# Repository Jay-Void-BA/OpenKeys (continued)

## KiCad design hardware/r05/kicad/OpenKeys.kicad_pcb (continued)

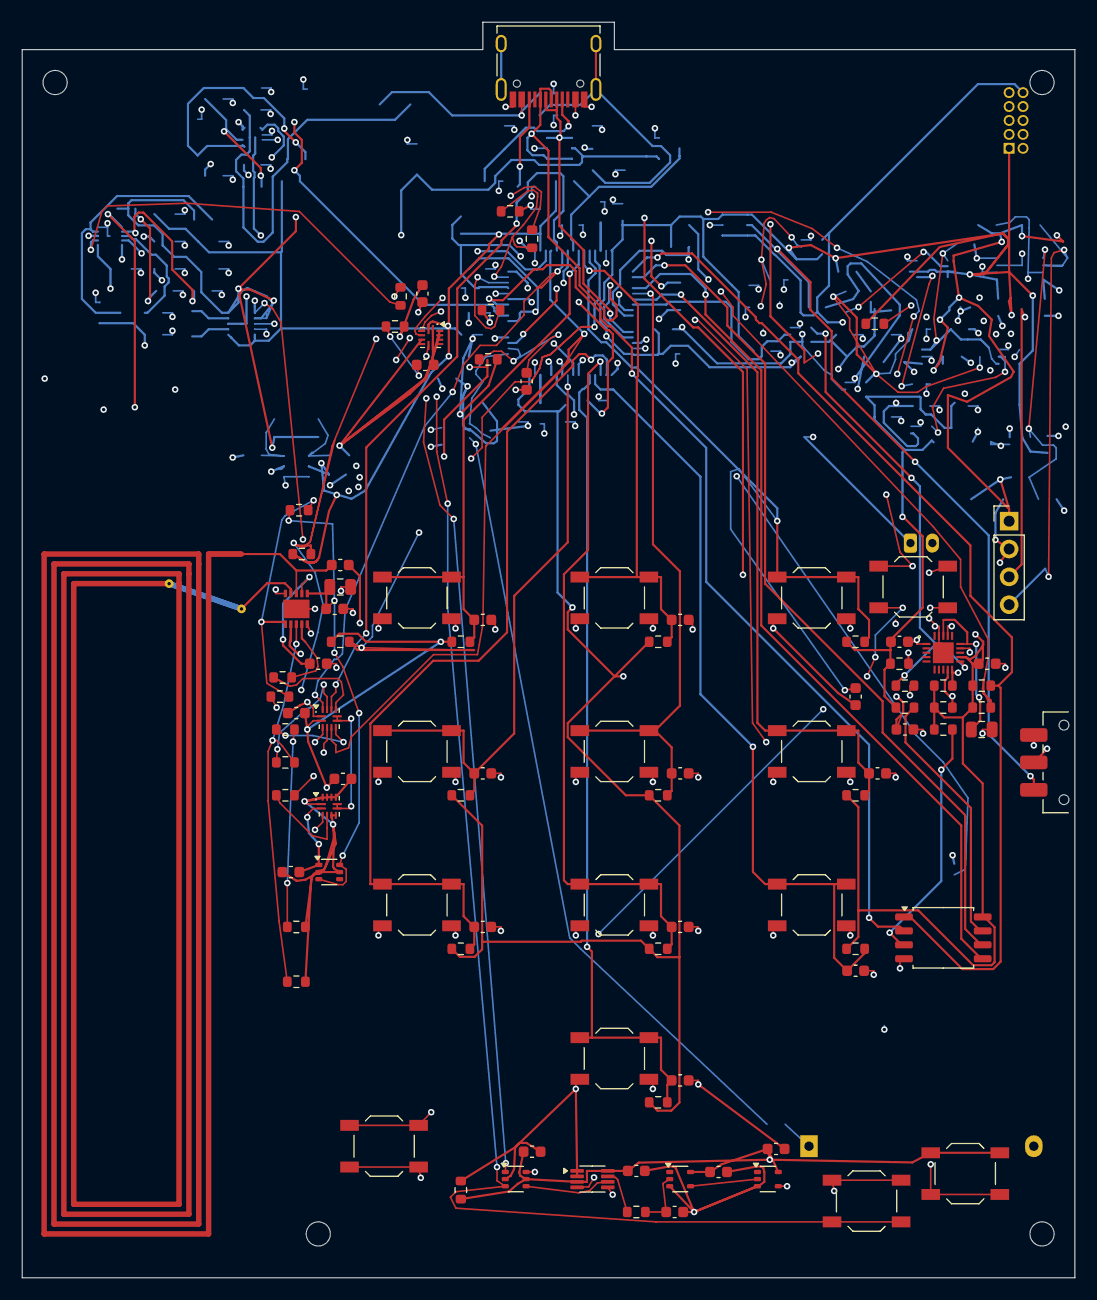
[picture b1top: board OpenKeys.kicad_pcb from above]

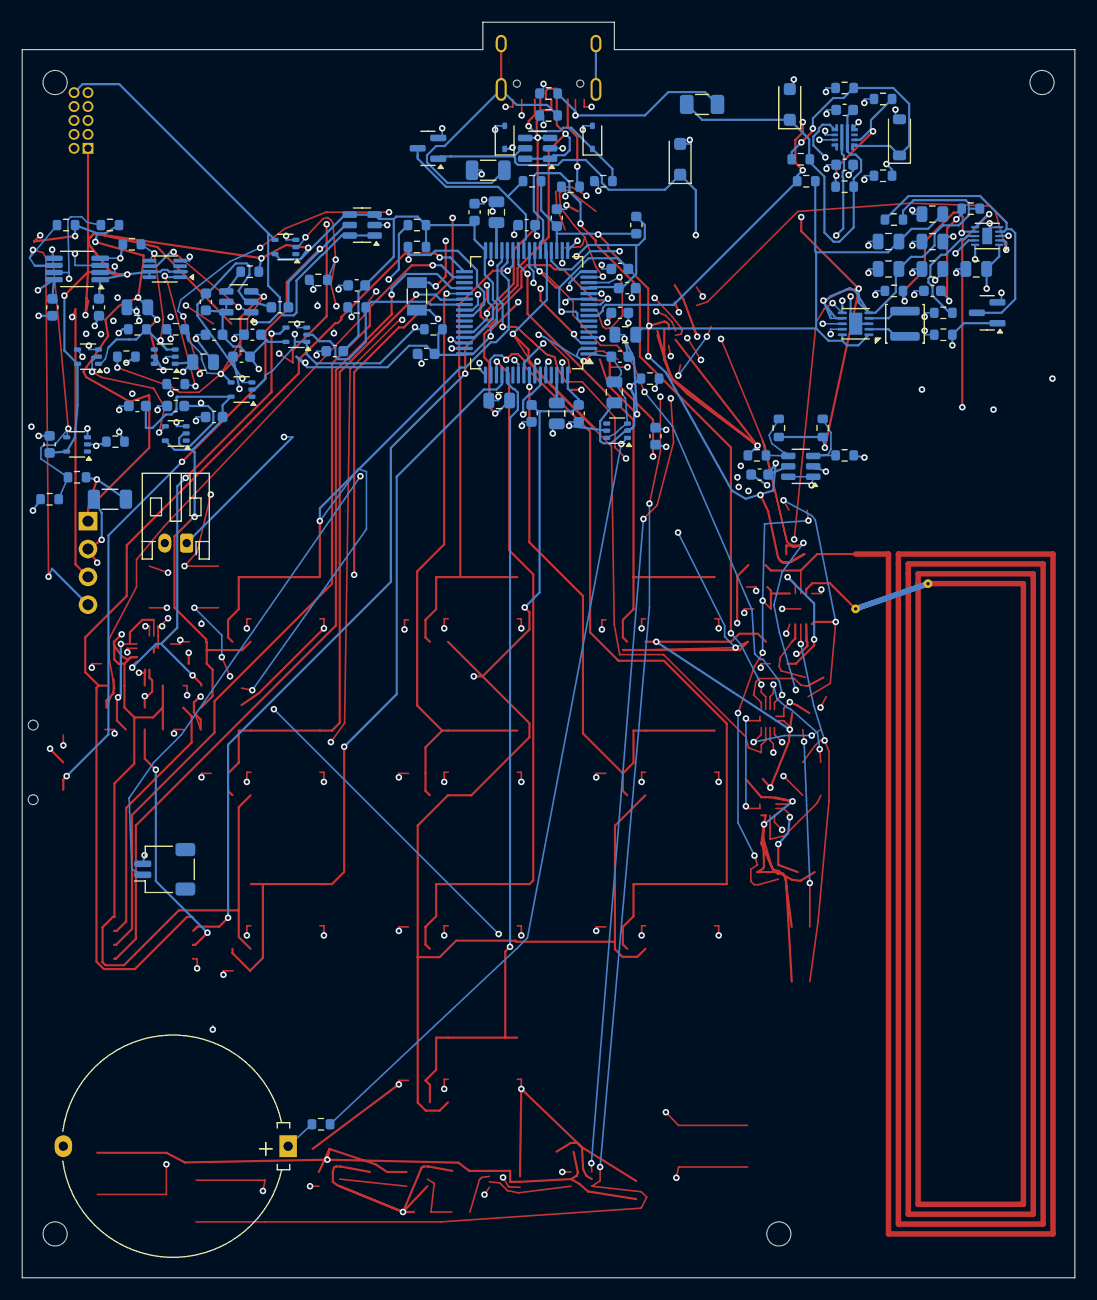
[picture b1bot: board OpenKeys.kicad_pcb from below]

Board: 4 copper layers, 96.0 x 114.5 mm, 213 parts (114 on the bottom side), 111 nets.

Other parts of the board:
H1, H2, H3, H4: MountingHole_2.2mm_M2

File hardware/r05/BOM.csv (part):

ref,value,footprint,sheet,dnp,note
J1,HRO TYPE-C-31-M-12,Connector_USB:USB_C_Receptacle_HRO_TYPE-C-31-M-12,01-usb,False,Only external data socket; qualify manufacturer drawing and sample
U1,USBLC6-2SC6,Package_TO_SOT_SMD:SOT-23-6,01-usb,False,
R1,5.1k 1%,Resistor_SMD:R_0603_1608Metric,01-usb,False,
R2,5.1k 1%,Resistor_SMD:R_0603_1608Metric,01-usb,False,
R3,1M,Resistor_SMD:R_0603_1608Metric,01-usb,False,
C1,1nF / 2kV,Capacitor_SMD:C_1206_3216Metric,01-usb,False,KEMET C1206C102KGRACTU;1206;2kV X7R10percent
Q1,2N7002,Package_TO_SOT_SMD:SOT-23,01-usb,False,
R4,100k,Resistor_SMD:R_0603_1608Metric,01-usb,False,
R5,1M,Resistor_SMD:R_0603_1608Metric,01-usb,False,
D1,SMF5.0A,Diode_SMD:D_SOD-123F,01-usb,False,
D2,PESD5V0S1BA,Diode_SMD:D_SOD-323,01-usb,False,
D3,PESD5V0S1BA,Diode_SMD:D_SOD-323,01-usb,False,
F1,250mA hold - qualify I2t,Fuse:Fuse_1206_3216Metric,02-power,False,
U2,BQ25185DLHR,Package_DFN_QFN:Texas_DLH0010A_WSON-10-1EP_2.2x2mm_P0.4mm_EP0.9x1.5mm,02-power,False,TI SLUSF65B table6-1:24k=4.2V/input100mA; ISET3k=target100mA before input DPM
J2,Adafruit 1578 protected 1S 500mAh,Connector_JST:JST_PH_S2B-PH-K_1x02_P2.00mm_Horizontal,02-power,False,Factory-protected pack; JST-PH2 polarity must be measured before mating. Pack body29x36x4.75mm; reserve32x40x6.5mm. No bare-cell substitution
J6,103AT-2 external battery thermistor,Connector_JST:JST_SH_SM02B-SRSS-TB_1x02-1MP_P1.00mm_Horizontal,02-power,False,"Semitec103AT-2 10k/B3435 insulated thermal contact to pouch, factory crimped SH harness. Not an ambient-only board thermistor"
R6,24k 1%,Resistor_SMD:R_0603_1608Metric,02-power,False,
R7,3.00k 1%,Resistor_SMD:R_0603_1608Metric,02-power,False,
R8,100k,Resistor_SMD:R_0603_1608Metric,02-power,False,
Q2,2N7002,Package_TO_SOT_SMD:SOT-23,02-power,False,
R9,100k,Resistor_SMD:R_0603_1608Metric,02-power,False,
C2,1uF 10V,Capacitor_SMD:C_0805_2012Metric,02-power,False,
C3,10uF 6.3V,Capacitor_SMD:C_0805_2012Metric,02-power,False,
C4,10uF 10V,Capacitor_SMD:C_0805_2012Metric,02-power,False,
SW1,OFF / ON,Button_Switch_SMD:SW_SPDT_CK_JS102011SAQN,02-power,False,
U3,TPS63031DSK (3.3 V),Package_SON:WSON-10-1EP_2.5x2.5mm_P0.5mm_EP1.2x2mm,02-power,False,"PS/SYNC tied to VIN: forced PWM, guaranteed DC output3.267..3.333V before load/transient effects. GND power-save mode has wider -3/+6percent range and is not approved here."
R10,0R,Resistor_SMD:R_0603_1608Metric,02-power,False,
L1,1.5uH Isat>=1.5A,Inductor_SMD:L_Sunlord_SWPA3015S,02-power,False,
C5,10uF 10V,Capacitor_SMD:C_0805_2012Metric,02-power,False,
C6,100nF,Capacitor_SMD:C_0603_1608Metric,02-power,False,
C7,10uF 6.3V,Capacitor_SMD:C_0805_2012Metric,02-power,False,
C8,10uF 6.3V,Capacitor_SMD:C_0805_2012Metric,02-power,False,
U4,STM32H573RIT6,Package_QFP:LQFP-64_10x10mm_P0.5mm,03-mcu,False,"H573 pin62=VCAP2, no PB9; SE PB6/PB7; LCD PA8/PC9. Recheck complete alternate functions before firmware target release"
C9,100nF,Capacitor_SMD:C_0603_1608Metric,03-mcu,False,
C10,100nF,Capacitor_SMD:C_0603_1608Metric,03-mcu,False,
C11,100nF,Capacitor_SMD:C_0603_1608Metric,03-mcu,False,
C12,100nF,Capacitor_SMD:C_0603_1608Metric,03-mcu,False,
C13,100nF,Capacitor_SMD:C_0603_1608Metric,03-mcu,False,
C14,4.7uF,Capacitor_SMD:C_0805_2012Metric,03-mcu,False,
C15,2.2uF low ESR,Capacitor_SMD:C_0805_2012Metric,03-mcu,False,
C16,2.2uF low ESR,Capacitor_SMD:C_0805_2012Metric,03-mcu,False,
C17,100nF,Capacitor_SMD:C_0603_1608Metric,03-mcu,False,
C18,1uF,Capacitor_SMD:C_0805_2012Metric,03-mcu,False,
FB1,600R@100MHz,Inductor_SMD:L_0603_1608Metric,03-mcu,False,
R11,10k,Resistor_SMD:R_0603_1608Metric,03-mcu,False,
C19,10nF - qualify reset timing,Capacitor_SMD:C_0603_1608Metric,03-mcu,False,
R12,10k,Resistor_SMD:R_0603_1608Metric,03-mcu,False,
J3,Internal SWD - DNP production,Connector_PinHeader_1.27mm:PinHeader_2x05_P1.27mm_Vertical,03-mcu,True,Internal manufacturing access only; close debug lifecycle before user secrets
Y1,ABS07-32.768KHZ-6-T,Crystal:Crystal_SMD_3215-2Pin_3.2x1.5mm,03-mcu,False,LSE for backup RTC and tamper. RTC validity/rollback must be qualified. 9pF loading provisional; qualify startup/drive across temperature
C20,9pF C0G - tune,Capacitor_SMD:C_0603_1608Metric,03-mcu,False,
C21,9pF C0G - tune,Capacitor_SMD:C_0603_1608Metric,03-mcu,False,
U5,SE051C2HQ1/Z01XDZ,OpenKeys:SE050_SOT1969-1_HX2QFN20,04-se-storage,False,"SE051 Rev2.0 table3/SOT1969-1: unused RF1/17 and RST14 grounded; VOUT15 to VCC18 only. Target C2 OEF A8FA/Applet7.2 full feature. Identity, PIN ACL/retries, RSA4096 and per-device SCP commissioning still require qualification"
U6,W25Q64JVSSIQ,Package_SO:SOIC-8_5.3x5.3mm_P1.27mm,04-se-storage,False,
R13,4.7k,Resistor_SMD:R_0603_1608Metric,04-se-storage,False,
R14,4.7k,Resistor_SMD:R_0603_1608Metric,04-se-storage,False,
R15,100k,Resistor_SMD:R_0603_1608Metric,04-se-storage,False,
R16,47k,Resistor_SMD:R_0603_1608Metric,04-se-storage,False,
R17,47k,Resistor_SMD:R_0603_1608Metric,04-se-storage,False,
R18,47k,Resistor_SMD:R_0603_1608Metric,04-se-storage,False,
R19,10k,Resistor_SMD:R_0603_1608Metric,04-se-storage,False,
R20,10k,Resistor_SMD:R_0603_1608Metric,04-se-storage,False,
C22,100nF,Capacitor_SMD:C_0603_1608Metric,04-se-storage,False,
C23,100nF,Capacitor_SMD:C_0603_1608Metric,04-se-storage,False,
C24,1uF,Capacitor_SMD:C_0805_2012Metric,04-se-storage,False,
C25,100nF,Capacitor_SMD:C_0603_1608Metric,04-se-storage,False,
U7,FM11NC08S (DFN10 + EP),OpenKeys:FM11NC08S_DFN10_3x3_EP1.7x2.4,05-nfc,False,"Original candidate lands from Fudan v1.0 p9: package3x3,pitch0.5,EP rotated1.7x2.4; confirm supplier revision, sample orientation, paste and DFM. All five host signals and VCC cross independent isolation on sheet13; VOUT remains local"
J4,Integral 13.56MHz PCB loop,OpenKeys:NFC_PCB_Loop_4T_62x15,05-nfc,False,Integral copper4-turn coil; no purchased connector. Separate RF-only region. Initial matching model must be measured in assembled shell.
C26,100nF,Capacitor_SMD:C_0603_1608Metric,05-nfc,False,
C27,1uF,Capacitor_SMD:C_0805_2012Metric,05-nfc,False,
C28,100nF 10V,Capacitor_SMD:C_0603_1608Metric,05-nfc,False,
C29,56pF C0G 50V initial match,Capacitor_SMD:C_0603_1608Metric,05-nfc,False,
R21,47k,Resistor_SMD:R_0603_1608Metric,05-nfc,False,
R22,47k,Resistor_SMD:R_0603_1608Metric,05-nfc,False,
J7,DFR0555 V1.1 - OFFBOARD MODULE,Connector_PinHeader_2.54mm:PinHeader_1x04_P2.54mm_Vertical,06-trusted-ui,False,Internal keyed harness must follow VCC/GND/SCL/SDA; no external second data port. Module87x32x13mm. Qualify actual supply tolerance and revision.
R23,4.7k,Resistor_SMD:R_0603_1608Metric,06-trusted-ui,False,
R24,4.7k,Resistor_SMD:R_0603_1608Metric,06-trusted-ui,False,
SW2,KEY 1,Button_Switch_SMD:SW_SPST_TL3342,06-trusted-ui,False,Independent GPIO; physical release events only. No matrix and no host key injection.
R25,47k,Resistor_SMD:R_0603_1608Metric,06-trusted-ui,False,
C30,10nF,Capacitor_SMD:C_0603_1608Metric,06-trusted-ui,False,
SW3,KEY 2,Button_Switch_SMD:SW_SPST_TL3342,06-trusted-ui,False,Independent GPIO; physical release events only. No matrix and no host key injection.
R26,47k,Resistor_SMD:R_0603_1608Metric,06-trusted-ui,False,
C31,10nF,Capacitor_SMD:C_0603_1608Metric,06-trusted-ui,False,
SW4,KEY 3,Button_Switch_SMD:SW_SPST_TL3342,06-trusted-ui,False,Independent GPIO; physical release events only. No matrix and no host key injection.
R27,47k,Resistor_SMD:R_0603_1608Metric,06-trusted-ui,False,
C32,10nF,Capacitor_SMD:C_0603_1608Metric,06-trusted-ui,False,
SW5,KEY 4,Button_Switch_SMD:SW_SPST_TL3342,06-trusted-ui,False,Independent GPIO; physical release events only. No matrix and no host key injection.
R28,47k,Resistor_SMD:R_0603_1608Metric,06-trusted-ui,False,
C33,10nF,Capacitor_SMD:C_0603_1608Metric,06-trusted-ui,False,
SW6,KEY 5,Button_Switch_SMD:SW_SPST_TL3342,06-trusted-ui,False,Independent GPIO; physical release events only. No matrix and no host key injection.
R29,47k,Resistor_SMD:R_0603_1608Metric,06-trusted-ui,False,
C34,10nF,Capacitor_SMD:C_0603_1608Metric,06-trusted-ui,False,
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
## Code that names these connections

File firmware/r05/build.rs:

use sha2::{Digest, Sha256};
use std::{env, fs, path::PathBuf};

fn main() {
    println!("cargo:rerun-if-changed=build.rs");
    let here = PathBuf::from(env!("CARGO_MANIFEST_DIR"));
    let root = here.join("../..");
    let contract = here.join("board-contract.sha256");
    println!("cargo:rerun-if-changed={}", contract.display());
    let contract = fs::read_to_string(contract).expect("R05 reviewed board contract is missing");
    assert_eq!(
        contract.lines().count(),
        2,
        "Expected PCB and pinout bindings"
    );
    let names: Vec<_> = contract
        .lines()
        .map(|row| row.split_once("  ").unwrap().1)
        .collect();
    assert_eq!(
        names,
        [
            "hardware/r05/kicad/OpenKeys.kicad_pcb",
            "hardware/r05/pinout.csv"
        ]
    );
    for row in contract.lines() {
        let (expected, name) = row.split_once("  ").expect("Invalid contract row");
        assert!(name.starts_with("hardware/r05/"));
        assert!(!name.contains(".."));
        let path = root.join(name);
        println!("cargo:rerun-if-changed={}", path.display());
        let actual = format!("{:x}", Sha256::digest(fs::read(path).unwrap()));
        assert_eq!(
            actual, expected,
            "R05 hardware changed; review and freeze a new contract"
        );
    }
    let csv = fs::read_to_string(root.join("hardware/r05/pinout.csv")).unwrap();
    let rows: Vec<Vec<&str>> = csv
        .lines()
        .skip(1)
        .map(|r| r.split(',').collect())
        .collect();
    // Independent required-function list for the diagnostic and reserved NFC
    // interface. The CSV comes from the actual MCU schematic. NFC protocol
    // operation is still disabled; checking its pins does not implement it.
    for (signal, gpio, pin, function) in [
        ("BTN1_N", "PB0", "26", "power / GPIO / dedicated"),
        ("BTN2_N", "PB1", "27", "power / GPIO / dedicated"),
        ("BTN3_N", "PB2", "28", "power / GPIO / dedicated"),
        ("BTN4_N", "PB5", "57", "power / GPIO / dedicated"),
        ("BTN5_N", "PC6", "37", "power / GPIO / dedicated"),
        ("BTN6_N", "PC7", "38", "power / GPIO / dedicated"),
        ("BTN7_N", "PA15", "50", "power / GPIO / dedicated"),
        ("BTN8_N", "PC10", "51", "power / GPIO / dedicated"),
        ("BTN9_N", "PC11", "52", "power / GPIO / dedicated"),
        ("BTN0_N", "PC12", "53", "power / GPIO / dedicated"),
        ("LCD_RELEASE", "PC3", "11", "power / GPIO / dedicated"),
        ("LCD_ARM_CLK", "PC4", "24", "power / GPIO / dedicated"),
        ("LCD_HOST_SCL", "PA8", "41", "I2C3_SCL AF4"),
        ("LCD_HOST_SDA", "PC9", "40", "I2C3_SDA AF4"),
        ("SE_ENABLE_REQUEST", "PC8", "39", "power / GPIO / dedicated"),
        ("CHARGE_ENABLE", "PB4", "56", "power / GPIO / dedicated"),
        (
            "CASE_TAMP_RETURN",
            "PC13",
            "2",
            "TAMP_IN1 dedicated/VBAT; active loop from OUT4",
        ),
        (
            "TAMP_DRIVE_RAW",
            "PA1",
            "15",
            "TAMP_OUT4 dedicated/VBAT; no GPIO waveform",
        ),
        (
            "BATTERY_SENSE",
            "PA0",
            "14",
            "ADC1_INP0 analog; main cell voltage only",
        ),
        ("USB_GUARD_FAULT_N", "PC0", "8", "power / GPIO / dedicated"),
        ("FLASH_CS_N", "PB12", "33", "power / GPIO / dedicated"),
        ("FLASH_SCK", "PB13", "34", "SPI2_SCK AF5"),
        ("FLASH_MOSI", "PB15", "36", "SPI2_MOSI AF5"),
        ("FLASH_MISO", "PC2", "10", "SPI2_MISO AF5"),
        ("NFC_CS_N", "PA4", "20", "power / GPIO / dedicated"),
        ("NFC_SCK", "PA5", "21", "SPI1_SCK AF5"),
        ("NFC_MISO", "PA6", "22", "SPI1_MISO AF5"),
        ("NFC_MOSI", "PA7", "23", "SPI1_MOSI AF5"),
        ("NFC_IRQ_N", "PB10", "29", "power / GPIO / dedicated"),
    ] {
        let matching: Vec<_> = rows.iter().filter(|r| r[2] == signal).collect();
        assert_eq!(
            matching.len(),
            1,
            "Missing or duplicate R05 signal: {signal}"
        );
        assert_eq!(matching[0][0], pin);
        assert_eq!(matching[0][1], gpio);
        assert_eq!(matching[0][3], function);
    }
    assert!(!csv.contains("FP_") && !csv.contains("LCD_RESET_N"));
    assert!(
        rows.iter().all(|row| row[1] != "PC1"),
        "PC1 is unused, not backup tamper"
    );
    if env::var_os("CARGO_FEATURE_R05_DIAGNOSTICS").is_none() {
        return;
    }
    assert_eq!(env::var("TARGET").unwrap(), "thumbv8m.main-none-eabihf");
    let output = PathBuf::from(env::var_os("OUT_DIR").unwrap());
    // Bring-up ONLY. Never use this OPEN/TZEN=0 map for owner secrets.
    fs::write(output.join("memory.x"), "MEMORY {\n FLASH : ORIGIN = 0x08000000, LENGTH = 2048K\n RAM : ORIGIN = 0x20000000, LENGTH = 256K\n}\n").unwrap();
    println!("cargo:rustc-link-search={}", output.display());
    println!("cargo:rustc-link-arg-bin=openkeys-r05-diagnostics=-Tlink.x");
}

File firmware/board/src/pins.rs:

// Generated from the frozen R04 pinout.csv; do not infer a different pinmux.
// Board SHA256: 6c2a93a63f343cf0401eae8c92dc1da6f5db145604ee9b0e8b9bd08b76f4bde4
#[derive(Clone, Copy, Debug, PartialEq, Eq)]
pub struct Pin {
    pub package_pin: u8,
    pub port: u8,
    pub bit: u8,
    pub alternate: Option<u8>,
}
pub const BOARD_REVISION: &str = "0.4";
pub const BOARD_SHA256: &str = "6c2a93a63f343cf0401eae8c92dc1da6f5db145604ee9b0e8b9bd08b76f4bde4";
pub const PINOUT_SHA256: &str = "015f236a2066e38bd63a31aea3ea134474402bfe2becfdf4af9b7557d0dacac5";
pub const CASE_CLOSED: Pin = Pin {
    package_pin: 2,
    port: b'C',
    bit: 13,
    alternate: None,
};
pub const LSE_IN: Pin = Pin {
    package_pin: 3,
    port: b'C',
    bit: 14,
    alternate: None,
};
pub const LSE_OUT: Pin = Pin {
    package_pin: 4,
    port: b'C',
    bit: 15,
    alternate: None,
};
pub const USB_GUARD_FAULT_N: Pin = Pin {
    package_pin: 8,
    port: b'C',
    bit: 0,
    alternate: None,
};
pub const NRST: Pin = Pin {
    package_pin: 9,
    port: b'C',
    bit: 1,
    alternate: None,
};
pub const FLASH_MISO: Pin = Pin {
    package_pin: 10,
    port: b'C',
    bit: 2,
    alternate: Some(5),
};
pub const LCD_RESET_N: Pin = Pin {
    package_pin: 11,
    port: b'C',
    bit: 3,
    alternate: None,
};
pub const CHG_STAT1_N: Pin = Pin {
    package_pin: 16,
    port: b'A',
    bit: 2,
    alternate: None,
};
pub const CHG_STAT2_N: Pin = Pin {
    package_pin: 17,
    port: b'A',
    bit: 3,
    alternate: None,
};
pub const NFC_CS_N: Pin = Pin {
    package_pin: 20,
    port: b'A',
    bit: 4,
    alternate: None,
};
pub const NFC_SCK: Pin = Pin {
    package_pin: 21,
    port: b'A',
    bit: 5,
    alternate: Some(5),
};
pub const NFC_MISO: Pin = Pin {
    package_pin: 22,
    port: b'A',
    bit: 6,
    alternate: Some(5),
};
pub const NFC_MOSI: Pin = Pin {
    package_pin: 23,
    port: b'A',
    bit: 7,
    alternate: Some(5),
};
pub const LCD_BACKLIGHT: Pin = Pin {
    package_pin: 24,
    port: b'C',
    bit: 4,
    alternate: None,
};
pub const VBUS_PRESENT_N: Pin = Pin {
    package_pin: 25,
    port: b'C',
    bit: 5,
    alternate: None,
};
pub const BTN1_N: Pin = Pin {
    package_pin: 26,
    port: b'B',
    bit: 0,
    alternate: None,
};
pub const BTN2_N: Pin = Pin {
    package_pin: 27,
    port: b'B',
    bit: 1,
    alternate: None,
};
pub const BTN3_N: Pin = Pin {
    package_pin: 28,
    port: b'B',
    bit: 2,
    alternate: None,
};
pub const NFC_IRQ_N: Pin = Pin {
    package_pin: 29,
    port: b'B',
    bit: 10,
    alternate: None,
};
pub const FLASH_CS_N: Pin = Pin {
    package_pin: 33,
    port: b'B',
    bit: 12,
    alternate: None,
};
pub const FLASH_SCK: Pin = Pin {
    package_pin: 34,
    port: b'B',
    bit: 13,
    alternate: Some(5),
};
pub const FLASH_MOSI: Pin = Pin {
    package_pin: 36,
    port: b'B',
    bit: 15,
    alternate: Some(5),
};
pub const FP_IRQ: Pin = Pin {
    package_pin: 37,
    port: b'C',
    bit: 6,
    alternate: None,
};
pub const FP_RESET_N: Pin = Pin {
    package_pin: 38,
    port: b'C',
    bit: 7,
    alternate: None,
};
pub const SE_ENABLE_REQUEST: Pin = Pin {
    package_pin: 39,
    port: b'C',
    bit: 8,
    alternate: None,
};
pub const LCD_SDA: Pin = Pin {
    package_pin: 40,
    port: b'C',
    bit: 9,
    alternate: Some(4),
};
pub const LCD_SCL: Pin = Pin {
    package_pin: 41,
    port: b'A',
    bit: 8,
    alternate: Some(4),
};
pub const USB_DM: Pin = Pin {
    package_pin: 44,
    port: b'A',
    bit: 11,
    alternate: Some(10),
};
pub const USB_DP: Pin = Pin {
    package_pin: 45,
    port: b'A',
    bit: 12,
    alternate: Some(10),
};
pub const SWDIO: Pin = Pin {
    package_pin: 46,
    port: b'A',
    bit: 13,
    alternate: None,
};
pub const SWCLK: Pin = Pin {
    package_pin: 49,
    port: b'A',
    bit: 14,
    alternate: None,
};
pub const FP_CS_N: Pin = Pin {
    package_pin: 50,
    port: b'A',
    bit: 15,
    alternate: None,
};
pub const FP_SCK: Pin = Pin {
    package_pin: 51,
    port: b'C',
    bit: 10,
    alternate: Some(6),
};
pub const FP_MISO: Pin = Pin {
    package_pin: 52,
    port: b'C',
    bit: 11,
    alternate: Some(6),
};
pub const FP_MOSI: Pin = Pin {
    package_pin: 53,
    port: b'C',
    bit: 12,
    alternate: Some(6),
};
pub const SWO: Pin = Pin {
    package_pin: 55,
    port: b'B',
    bit: 3,
    alternate: None,
};
pub const CHARGE_ENABLE: Pin = Pin {
    package_pin: 56,
    port: b'B',
    bit: 4,
    alternate: None,
};
pub const BTN4_N: Pin = Pin {
    package_pin: 57,
    port: b'B',
    bit: 5,
    alternate: None,
};
pub const SE_SCL: Pin = Pin {
    package_pin: 58,
    port: b'B',
    bit: 6,
    alternate: Some(4),
};
pub const SE_SDA: Pin = Pin {
    package_pin: 59,
    port: b'B',
    bit: 7,
    alternate: Some(4),
};
pub const PIN_MAP: &[(&str, Pin)] = &[
    ("CASE_CLOSED", CASE_CLOSED),
    ("LSE_IN", LSE_IN),
    ("LSE_OUT", LSE_OUT),
    ("USB_GUARD_FAULT_N", USB_GUARD_FAULT_N),
    ("NRST", NRST),
    ("FLASH_MISO", FLASH_MISO),
    ("LCD_RESET_N", LCD_RESET_N),
    ("CHG_STAT1_N", CHG_STAT1_N),
    ("CHG_STAT2_N", CHG_STAT2_N),
    ("NFC_CS_N", NFC_CS_N),
    ("NFC_SCK", NFC_SCK),
    ("NFC_MISO", NFC_MISO),
    ("NFC_MOSI", NFC_MOSI),
    ("LCD_BACKLIGHT", LCD_BACKLIGHT),
    ("VBUS_PRESENT_N", VBUS_PRESENT_N),
    ("BTN1_N", BTN1_N),
    ("BTN2_N", BTN2_N),
    ("BTN3_N", BTN3_N),
    ("NFC_IRQ_N", NFC_IRQ_N),
    ("FLASH_CS_N", FLASH_CS_N),
    ("FLASH_SCK", FLASH_SCK),
    ("FLASH_MOSI", FLASH_MOSI),
    ("FP_IRQ", FP_IRQ),
    ("FP_RESET_N", FP_RESET_N),
    ("SE_ENABLE_REQUEST", SE_ENABLE_REQUEST),
    ("LCD_SDA", LCD_SDA),
    ("LCD_SCL", LCD_SCL),
    ("USB_DM", USB_DM),
    ("USB_DP", USB_DP),
    ("SWDIO", SWDIO),
    ("SWCLK", SWCLK),
    ("FP_CS_N", FP_CS_N),
    ("FP_SCK", FP_SCK),
    ("FP_MISO", FP_MISO),
    ("FP_MOSI", FP_MOSI),
    ("SWO", SWO),
    ("CHARGE_ENABLE", CHARGE_ENABLE),
    ("BTN4_N", BTN4_N),
    ("SE_SCL", SE_SCL),
    ("SE_SDA", SE_SDA),
];

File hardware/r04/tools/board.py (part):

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 # Reserve normal exits from fine-pitch pads BEFORE GND fanout/general
 # routing can surround them. These are electrical tracks, not exclusions.
 iset=pin('R7',1)
 trace('CHG_ISET',[pin('U2',8),(12.5,17),(12.5+iset[1]-17,iset[1]),iset],.15)
 vina=pin('C6',1);r_vina=pin('R10',2)
 trace('REG_VINA',[pin('U3',8),(19.2,24),(20.2,23),vina],.15)
 trace('REG_VINA',[vina,(vina[0],r_vina[1]),r_vina],.15)
 for n,site in [(18,(54,36.2)),(15,(56.8,37.7))]:
  via('SE_CORE',site);trace('SE_CORE',[pin('U5',n),site],.15,p.F_Cu)
 trace('SE_CORE',[(54,36.2),(55.3,36.2),(56.8,37.7)],.2)
 trace('SE_CORE',[pin('C23',1),(54,36.2)],.2)
 trace('SE_CORE',[pin('C24',1),(57,37.5),(56.8,37.7)],.2)
 via('+3V3',(56.8,38.9));trace('+3V3',[pin('U5',12),(56.8,38.9)],.25,p.F_Cu)
 trace('+3V3',[(56.8,38.9),pin('C22',1)],.25)
 via('NFC_VOUT',(5.4,67.5));trace('NFC_VOUT',[pin('U7',2),(5.4,67.5)],.15,p.F_Cu)
 nfc_cap=pin('C28',1)
 trace('NFC_VOUT',[(5.4,67.5),(5.4,66.875),(7,nfc_cap[1]),nfc_cap],.15)
 # Electrical feed guards expose the in-core part of the fixed antenna to
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  assert math.dist(pin('U7',n),path[0])<.001
  trace(net,path,.15,p.F_Cu);via(net,path[-1])
 for n,site in [('A9',(31.55,6)),('A4',(36.45,6))]:
  trace('VBUS_RAW',[pin('J1',n),site],.3,p.F_Cu);via('VBUS_RAW',site)
 trace('VBUS_RAW',[(31.55,6),(36.45,6)],.3)
 via('VBUS_RAW',(24.6,3.5))
 trace('VBUS_RAW',[(24.6,3.5),pin('F1',1)],.3)
 trace('VBUS_RAW',[(31.55,6),(30.55,5),(26.1,5),(24.6,3.5)],.3,p.In2_Cu)
 # Explicit manufacturing rules, used by KiCad and Specctra export.
 project=json.loads((CAD/'OpenKeys.kicad_pro').read_text())
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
